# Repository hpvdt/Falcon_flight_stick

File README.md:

# Falcon Flight Stick
A custom-designed **flight control stick** for the Falcon Aircraft project — designing both **hardware and firmware** for force sensing, CAN communication, and USB HID joystick interfacing.

---

## Overview
The **Falcon Flight Stick** is a force-sensing joystick that measures user input via strain gauges and communicates with the aircraft’s control system through **CAN bus** or to a computer host via **USB-C**.  
This project demonstrates my ability to proficiently design, route, and program an embedded system from the ground up — including power delivery, signal integrity, and firmware architecture.

---

## Key Features
- **MCU Core:** STM32F103CBU6 managing all board-level events with an external 8Mhz Oscillator
- **Sensing System:** Three strain gauges read via a precision Texas Instruments ADS131M03IRUK ADC (32-bit SPI interface)  
- **Connectivity:**  
  - USB-C (HID joystick or virtual COM port)  
  - CAN bus daisy-chain communication  
- **Memory:** 1×128-byte EEPROM for calibration data 
- **Power System:**  
  - TI TPS62177 step-down converter for higher current ditial power
  - ADI LT1962 LDO (3.3V)  for low noise, low current analog power
  - Automatic protection between USB-C and LiPo (12V) sources 
- **PCB Stackup:** 4-layer board with separated analog/digital planes for signal integrity
- **Breakout Button Matrix:**
  - button matrix allowing for a hotswappable and fully customizable button interface on the joystick
  - Up to 25 individual buttons, all allowable for interrupts

---

## Hardware Design

### Hardware Repository
The latest hardware version is **Falcon Flight Stick Rev5**.  
Previous revisions were experimental or undocumented.

### Design Breakdown

The STM32 MCU is programmed through **ST-LinkV3 (SWD)** and communicates via **UART** for debug and development.  
Differential USB data lines enable HID or COM functionality, depending on firmware.  

Strain gauge signals are processed through a TI ADC, which triggers SPI reads via a DRDY interrupt.  
Processed values are sent to the servo controller board (via CAN) or USB interface.  

---

## Power Architecture

The power subsystem ensures stable operation from multiple sources:
- **12V LiPo (CAN chain)** or **5V USB-C**
- Both inputs are protected from backfeed
- Outputs:  
  - 3.3V Digital (MCU, logic)  
  - 3.3V Analog (ADC, strain gauge front-end)

These rails are physically isolated to minimize noise and ground-reference drift.

---

## Schematics
Full schematic set:  

---

## PCB Layout

### Summary
- 4-layer stackup for power and noise isolation  
- Separated analog/digital ground and power planes  
- Power trace widths sized by current draw  
- Labelled parts for developer readability  

### Views
**Full Layout:**  

**Layer 1: Signal**  

**Layer 2: Power**  

**Layer 3: GND / AGND**  

**Layer 4: Signal 2**  

---

## 3D Model

---

## Firmware (Planned / In Progress)

Example outline:
- USB HID joystick emulation via STM32 HAL  
- CAN message handling for actuator control  
- ADC data acquisition and digital filtering  
- EEPROM calibration storage  

---

## Tools Used
- **KiCad 8.0** – PCB and schematic design  
- **STM32CubeIDE** – Firmware development  & MCU pinout planning
- **JLCPCB** – Fabrication and assembly  
- **SolidWorks** – 3D mechanical integration  
- **GitHub / Git** – Version control  

---

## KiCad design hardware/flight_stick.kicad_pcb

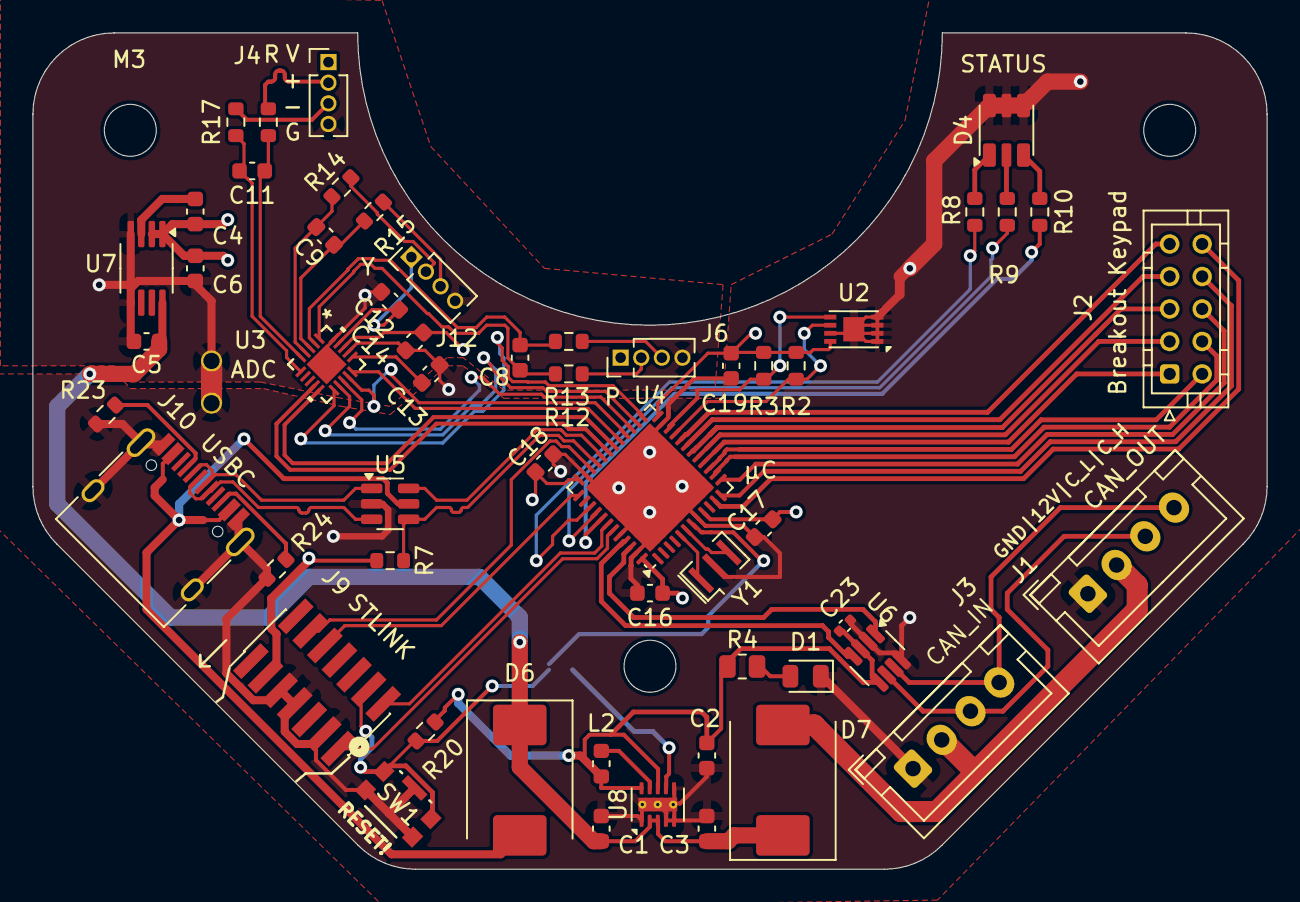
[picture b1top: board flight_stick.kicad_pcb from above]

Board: 4 copper layers, 76.0 x 51.5 mm, 60 parts (1 on the bottom side), 66 nets.

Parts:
C1, C3: 2.2u; C_0603_1608Metric
C2: 22u; C_0603_1608Metric
C4: 10n; C_0603_1608Metric
C5: 1u; C_0603_1608Metric
C6: 4.7u; C_0603_1608Metric
C8, C9, C11, C12, C14, C16, C17, C18, C19: 100n; C_0603_1608Metric
C13: 220n; C_0603_1608Metric
C23: 1u; C_0402_1005Metric
D1: GREEN_LED; LED_0805_2012Metric
D4: SMLVN6RGB; LED_ROHM_SMLVN6
D6, D7: SS34; D_SMC
H1, H2, H3: MountingHole; MountingHole_3.2mm_M3
J1, J3: Conn_01x04_Male; JST_XH_B4B-XH-A_1x04_P2.50mm_Vertical
J2: Conn_02x05_Odd_Even; JST_PHD_B10B-PHDSS_2x05_P2.00mm_Vertical
J4: Load Cell 3; PinHeader_1x04_P1.27mm_Vertical
J6: Load Cell 1; PinHeader_1x04_P1.27mm_Vertical
J9: Conn_ST_STDC14; PinHeader_2x07_P1.27mm_Vertical_SMD
J10: USB_C_Receptacle_USB2.0; USB_C_Receptacle_HRO_TYPE-C-31-M-12
J12: Load Cell 2; PinHeader_1x04_P1.27mm_Vertical
JP1: SolderJumper; SolderJumper-2_P1.3mm_Open_TrianglePad1.0x1.5mm
L2: 10uH; L_0603_1608Metric
NT1: NetTie_2; NetTie-2_THT_Pad1.0mm
R2, R3: 4.7k; R_0603_1608Metric
R4: 400; R_0805_2012Metric
R7: 1.5k; R_0603_1608Metric
R8, R9, R10: 200; R_0603_1608Metric
R12, R13, R14, R15, R16, R17: 1k; R_0603_1608Metric
R20: 10k; R_0603_1608Metric
R23, R24: 5.1K; R_0603_1608Metric
SW1: KMR223G LFG; KMR2_G_CNK
U2: AT24CS01-MAHM; DFN-8-1EP_3x2mm_P0.5mm_EP1.3x1.5mm
U3: ADS131M03IRUKx; QFN_WQFN_RUK_TEX
U4: STM32F103CBU6; QFN-48-1EP_7x7mm_P0.5mm_EP5.6x5.6mm
U5: USBLC6-2SC6; SOT-23-6
U6: TCAN3403; TSOT-23-8
U7: LT1962-3.3; MSOP-8_3x3mm_P0.65mm
U8: TPS62177DQC; WSON-10-1EP_2x3mm_P0.5mm_EP0.84x2.4mm_ThermalVias
Y1: 8M; Resonator_SMD_Murata_CSTxExxV-3Pin_3.0x1.1mm

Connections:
+3.3V: C2.1, C14.1, C16.2, C17.2, C18.2, C19.1, C23.1, J9.3 (VCC), L2.2, R2.1, R3.1, R4.1, R7.1, R20.1, U2.8 (VCC), U3.18 (DVDD), U4.9 (VDDA), U4.24 (VDD), U4.36 (VDD), U4.48 (VDD), U6.3 (V_{CC}), U6.5 (V_{IO}), U8.8 (~SLEEP), U8.10 (VOS)
+3.3VA: C4.1, C6.1, C12.1, J4.1, J6.1, J12.1, U3.19 (AVDD), U7.1 (OUT), U7.2 (SENSE)
+5V: D6.2 (A), J10.A4 (VBUS), J10.A9 (VBUS), J10.B4 (VBUS), J10.B9 (VBUS), U5.5 (VBUS)
+12V: D7.2 (A), J1.2, J3.2
/ADC_CS: U3.10 (~CS), U4.30 (PA9)
/ADC_DRDY: U3.11 (DRDY), U4.25 (PB12)
/ADC_MCO: U3.15 (CLKIN), U4.29 (PA8)
/ADC_MISO: U3.13 (DOUT), U4.27 (PB14)
/ADC_MOSI: U3.14 (DIN), U4.28 (PB15)
/ADC_RST: U3.9 (~RESET), U4.31 (PA10)
/ADC_SCK: U3.12 (SCLK), U4.26 (PB13)
/CAN_IO/CAN_H: J1.4, J3.4, U6.7 (CANH)
/CAN_IO/CAN_L: J1.3, J3.3, U6.6 (CANL)
/CAN_RX: U4.45 (PB8), U6.4 (RXD)
/CAN_TX: U4.46 (PB9), U6.1 (TXD)
/COMPRT_RX: J9.13 (VCP_RX), U4.43 (PB7)
/COMPRT_TX: J9.14 (VCP_TX), U4.42 (PB6)
/D+: J10.A6 (D+), J10.B6 (D+), U5.3 (I/O2)
/D-: J10.A7 (D-), J10.B7 (D-), U5.1 (I/O1)
/EEPROM_SCK: R2.2, U2.6 (SCL), U4.21 (PB10)
/EEPROM_SDA: R3.2, U2.5 (SDA), U4.22 (PB11)
/MTX_COL1: J2.2, U4.15 (PA5)
/MTX_COL2: J2.4, U4.14 (PA4)
/MTX_COL3: J2.6, U4.13 (PA3)
/MTX_COL4: J2.8, U4.12 (PA2)
/MTX_COL5: J2.10, U4.11 (PA1)
/MTX_ROW1: J2.1, U4.16 (PA6)
/MTX_ROW2: J2.3, U4.17 (PA7)
/MTX_ROW3: J2.5, U4.18 (PB0)
/MTX_ROW4: J2.7, U4.19 (PB1)
/MTX_ROW5: J2.9, U4.20 (PB2)
/OSC+: U4.5 (PD0), Y1.1
/OSC-: U4.6 (PD1), Y1.3
/PRC_DIO: J9.4 (JTMS/SWDIO), U4.34 (PA13)
/PRG_CLK: J9.6 (JCLK/SWCLK), U4.37 (PA14)
/Power/Vin_{pwr}: C1.1, C3.1, C5.1, D6.1 (K), D7.1 (K), U7.8 (IN), U8.2 (VIN), U8.3 (EN)
/RGB_B: R8.1, U4.39 (PB3)
/RGB_G: R10.1, U4.41 (PB5)
/RGB_R: R9.1, U4.40 (PB4)
/USBN: U4.32 (PA11), U5.6 (I/O1)
/USBP: R7.2, U4.33 (PA12), U5.4 (I/O2)
/~RESET: J9.12 (~RST), JP1.1 (A), R20.2, SW1.1, SW1.2, U4.7 (NRST)
GND: C1.2, C2.2, C3.2, C13.2, C14.2, C16.1, C17.1, C18.1, C19.2, C23.2, D1.1 (K), D4.4 (GK), D4.5 (RK), D4.6 (BK), J1.1, J3.1, J9.5 (GND), J9.7 (GND), J9.11 (GNDDetect), J10.A1 (GND), J10.A12 (GND), J10.B1 (GND), J10.B12 (GND), J10.S1 (SHIELD), NT1.2, R23.1, R24.1, SW1.3, SW1.4, SW1.5, U2.1 (A0), U2.2 (A1), U2.3 (A2), U2.4 (GND), U2.7 (WP), U2.9 (GND), U3.17 (DGND), U4.8 (VSSA), U4.23 (VSS), U4.35 (VSS), U4.44 (BOOT0), U4.47 (VSS), U4.49 (VSS), U5.2 (GND), U6.2 (GND), U6.8 (STB), U8.1 (PGND), U8.4 (NC), U8.5 (FB), U8.6 (AGND), U8.11 (PAD), Y1.2
GNDA: C5.2, C6.2, C12.2, J4.4, J6.4, J12.4, NT1.1, U3.20 (AGND), U3.21 (AGND), U7.4 (GND), U7.5 (~SHDN)
unnamed: D1.2 (A), R4.2
unnamed: D4.1 (BA), R8.2
unnamed: D4.3 (GA), R10.2
unnamed: D4.2 (RA), R9.2
unnamed: J4.2, R16.1
unnamed: J4.3, R17.1
unnamed: J6.2, R12.1
unnamed: J6.3, R13.1
unnamed: J10.A5 (CC1), R23.2
unnamed: J10.B5 (CC2), R24.2
unnamed: J12.2, R14.1
unnamed: J12.3, R15.1
unnamed: JP1.2 (B), U8.7 (PG)
unnamed: C8.1, R13.2, U3.2 (AIN0N)
unnamed: C8.2, R12.2, U3.1 (AIN0P)
unnamed: C9.1, R15.2, U3.3 (AIN1N)
unnamed: C9.2, R14.2, U3.4 (AIN1P)
unnamed: C11.1, R17.2, U3.6 (AIN2N)
unnamed: C11.2, R16.2, U3.5 (AIN2P)
unnamed: C13.1, U3.16 (CAP)
unnamed: C4.2, U7.3 (BYP)
unnamed: L2.1, U8.9 (SW)

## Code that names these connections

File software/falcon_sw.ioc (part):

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Mcu.Name=STM32F103CBUx
Mcu.Package=UFQFPN48
Mcu.UserName=STM32F103CBUx
PA1.GPIOParameters=GPIO_Label
PA1.GPIO_Label=MTX_COL5
PA1.Signal=GPIO_Output
PA10.GPIOParameters=GPIO_Label
PA10.GPIO_Label=ADC_RST
PA10.Signal=GPIO_Output
PA11.Mode=Device
PA11.Signal=USB_DM
PA12.Mode=Device
PA12.Signal=USB_DP
PA13.Mode=Serial_Wire
PA13.Signal=SYS_JTMS-SWDIO
PA14.Mode=Serial_Wire
PA14.Signal=SYS_JTCK-SWCLK
PA2.GPIOParameters=GPIO_Label
PA2.GPIO_Label=MTX_COL4
PA2.Signal=GPIO_Output
PA3.GPIOParameters=GPIO_Label
PA3.GPIO_Label=MTX_COL3
PA3.Signal=GPIO_Output
PA4.GPIOParameters=GPIO_Label
PA4.GPIO_Label=MTX_COL2
PA4.Signal=GPIO_Output
PA5.GPIOParameters=GPIO_Label
PA5.GPIO_Label=MTX_COL1
PA5.Signal=GPIO_Output
PA6.GPIOParameters=GPIO_Label
PA6.GPIO_Label=MTX_ROW1
PA6.Signal=GPIO_Input
PA7.GPIOParameters=GPIO_Label
PA7.GPIO_Label=MTX_ROW2
PA7.Signal=GPIO_Input
PA8.Mode=Clock-out
PA8.Signal=RCC_MCO
PA9.GPIOParameters=GPIO_Label
PA9.GPIO_Label=ADC_CS
PA9.Signal=GPIO_Output
PB0.GPIOParameters=GPIO_Label
PB0.GPIO_Label=MTX_ROW3
PB0.Signal=GPIO_Input
PB1.GPIOParameters=GPIO_Label
PB1.GPIO_Label=MTX_ROW4
PB1.Signal=GPIO_Input
PB10.GPIOParameters=GPIO_Label
PB10.GPIO_Label=EEP_I2C2_SCL
PB10.Mode=I2C
PB10.Signal=I2C2_SCL
PB11.GPIOParameters=GPIO_Label
PB11.GPIO_Label=EEP_I2C2_SDA
PB11.Mode=I2C
PB11.Signal=I2C2_SDA
PB12.GPIOParameters=GPIO_Label
PB12.GPIO_Label=ADC_DRDY_EXTI12
PB12.Signal=GPXTI12
PB13.Mode=Full_Duplex_Master
PB13.Signal=SPI2_SCK
PB14.Mode=Full_Duplex_Master
PB14.Signal=SPI2_MISO
PB15.Mode=Full_Duplex_Master
PB15.Signal=SPI2_MOSI
PB2.GPIOParameters=GPIO_Label
PB2.GPIO_Label=MTX_ROW5
PB2.Signal=GPIO_Input
PB3.Signal=S_TIM2_CH2
PB4.Signal=S_TIM3_CH1
PB5.GPIOParameters=GPIO_Label
PB5.GPIO_Label=RGB_PIN
PB5.Signal=GPIO_Output
PB6.Mode=Asynchronous
PB6.Signal=USART1_TX
PB7.Mode=Asynchronous
PB7.Signal=USART1_RX
PB8.Mode=CAN_Activate
PB8.Signal=CAN_RX
PB9.Mode=CAN_Activate
PB9.Signal=CAN_TX
PD0-OSC_IN.Mode=HSE-External-Oscillator
PD0-OSC_IN.Signal=RCC_OSC_IN
PD1-OSC_OUT.Mode=HSE-External-Oscillator
PD1-OSC_OUT.Signal=RCC_OSC_OUT
RCC.SYSCLKFreq_VALUE=48000000
RCC.SYSCLKSource=RCC_SYSCLKSOURCE_PLLCLK
board=custom

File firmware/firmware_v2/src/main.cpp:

/**
 * Falcon Flight Stick firmware_v2
 * STM32F103CBU6: UART hello + peripheral status, then loop: poll ADC -> 16-bit -> serial + RGB.
 *
 * Pinout:
 *   UART:    PB6 (TX), PB7 (RX)  - USART1 remapped
 *   ADC SPI: PB13 (SCLK), PB14 (MISO), PB15 (MOSI), CS=PA9, RESET=PA10, DRDY=PB12, MCO=PA7
 *   EEPROM:  PB10 (SCL), PB11 (SDA) - I2C2
 *   RGB:     PB3 (Blue), PB4 (Red), PB5 (Green)
 */

#include <Arduino.h>
#include <SPI.h>
#include <Wire.h>

// ---- UART (COM port via ST-Link) ----
#define UART_RX  PB7
#define UART_TX  PB6
HardwareSerial SerialUart(UART_RX, UART_TX);

// ---- ADC (ADS131M03) ----
#define ADC_CS    PA9
#define ADC_RST   PA10
#define ADC_DRDY  PB12
#define ADC_MCO   PA7
#define ADC_SCK   PB13
#define ADC_MISO  PB14
#define ADC_MOSI  PB15

SPIClass adc_spi(ADC_MOSI, ADC_MISO, ADC_SCK);

// ---- RGB LED ----
#define RGB_BLUE  PB3
#define RGB_RED   PB4
#define RGB_GREEN PB5

// ---- EEPROM I2C ----
#define EEPROM_SCL PB10
#define EEPROM_SDA PB11
#define EEPROM_ADDR 0x50

// ---- Timing ----
#define LOOP_DELAY_MS  2500

static void initUart(void);
static void initRgb(void);
static void initAdc(void);
static bool probeEeprom(void);
static void printStatus(bool adc_ok, bool eeprom_ok);
static void readAdcChannels(uint16_t* ch0, uint16_t* ch1, uint16_t* ch2);
static void setRgbFromAdc(uint16_t ch0, uint16_t ch1, uint16_t ch2);

void setup() {
  initUart();
  SerialUart.println("Hello");

  SerialUart.println("initRgb...");
  initRgb();
  SerialUart.println("initAdc...");
  initAdc();

  // Probe ADC: try one read (can block if ADC not connected / wrong wiring)
  SerialUart.println("readAdc...");
  uint16_t c0, c1, c2;
  readAdcChannels(&c0, &c1, &c2);
  bool adc_ok = (c0 != 0xFFFF && c1 != 0xFFFF && c2 != 0xFFFF) ||
                (c0 != 0x0000 && c1 != 0x0000 && c2 != 0x0000);  // avoid all 0 or all 1 as "no response"
  SerialUart.println("eeprom...");
  bool eeprom_ok = probeEeprom();

  printStatus(adc_ok, eeprom_ok);
}

void loop() {
  uint16_t ch0, ch1, ch2;
  readAdcChannels(&ch0, &ch1, &ch2);

  SerialUart.print("CH0=");
  SerialUart.print(ch0);
  SerialUart.print(" CH1=");
  SerialUart.print(ch1);
  SerialUart.print(" CH2=");
  SerialUart.println(ch2);

  setRgbFromAdc(ch0, ch1, ch2);
  delay(LOOP_DELAY_MS);
}

static void initUart(void) {
  SerialUart.begin(115200);
  while (!SerialUart)
    ;
}

static void initRgb(void) {
  pinMode(RGB_BLUE, OUTPUT);
  pinMode(RGB_RED, OUTPUT);
  pinMode(RGB_GREEN, OUTPUT);
  digitalWrite(RGB_BLUE, LOW);
  digitalWrite(RGB_RED, LOW);
  digitalWrite(RGB_GREEN, LOW);
}

static void initAdc(void) {
  pinMode(ADC_MCO, OUTPUT);
  RCC->CFGR &= ~RCC_CFGR_MCO;
  RCC->CFGR |= RCC_CFGR_MCO_SYSCLK;

  pinMode(ADC_CS, OUTPUT);
  pinMode(ADC_RST, OUTPUT);
  pinMode(ADC_DRDY, INPUT);
  digitalWrite(ADC_CS, HIGH);
  digitalWrite(ADC_RST, HIGH);

  digitalWrite(ADC_RST, LOW);
  delay(10);
  digitalWrite(ADC_RST, HIGH);
  delay(10);

  adc_spi.begin();
  delay(50);  // let ADC settle after reset before first SPI read
}

static bool probeEeprom(void) {
  Wire.begin((int)EEPROM_SDA, (int)EEPROM_SCL);
#if defined(WIRE_HAS_TIMEOUT)
  Wire.setWireTimeout(500, true);  // 500 us, reset on timeout so we don't hang
#endif
  Wire.beginTransmission((uint8_t)EEPROM_ADDR);
  uint8_t err = Wire.endTransmission();
  return (err == 0);
}

static void printStatus(bool adc_ok, bool eeprom_ok) {
  SerialUart.print("ADC: ");
  SerialUart.println(adc_ok ? "OK" : "FAIL");
  SerialUart.print("EEPROM: ");
  SerialUart.println(eeprom_ok ? "OK" : "FAIL/skip");
  SerialUart.println("RGB: OK");
  SerialUart.println("---");
}

/**
 * ADS131M03: 3 channels, 24-bit each. SPI frame: send null cmd (0x2000), read status + 3×24-bit.
 * We use 16-bit transfers: 1 status + 6 words for CH0/CH1/CH2 (each channel = 2×16-bit, 24-bit data).
 * 24-bit value = (high_word << 8) | (low_word >> 8). Normalize to 16-bit: take top 16 bits (>> 8).
 */
static void readAdcChannels(uint16_t* ch0, uint16_t* ch1, uint16_t* ch2) {
  digitalWrite(ADC_CS, LOW);
  delayMicroseconds(1);

  const uint16_t null_cmd = 0x2000;
  uint16_t w0 = adc_spi.transfer16(null_cmd);  // status
  uint16_t w1 = adc_spi.transfer16(null_cmd);  // CH0 high
  uint16_t w2 = adc_spi.transfer16(null_cmd);  // CH0 low
  uint16_t w3 = adc_spi.transfer16(null_cmd);  // CH1 high
  uint16_t w4 = adc_spi.transfer16(null_cmd);  // CH1 low
  uint16_t w5 = adc_spi.transfer16(null_cmd);  // CH2 high
  uint16_t w6 = adc_spi.transfer16(null_cmd);  // CH2 low

  digitalWrite(ADC_CS, HIGH);

  (void)w0;
  uint32_t v0_24 = ((uint32_t)w1 << 8) | (w2 >> 8);
  uint32_t v1_24 = ((uint32_t)w3 << 8) | (w4 >> 8);
  uint32_t v2_24 = ((uint32_t)w5 << 8) | (w6 >> 8);

  *ch0 = (uint16_t)(v0_24 >> 8);
  *ch1 = (uint16_t)(v1_24 >> 8);
  *ch2 = (uint16_t)(v2_24 >> 8);
}

/** CH0->R, CH1->G, CH2->B. Simple: above threshold (e.g. mid-scale) turn on, else off. */
static void setRgbFromAdc(uint16_t ch0, uint16_t ch1, uint16_t ch2) {
  const uint16_t thresh = 32768;
  digitalWrite(RGB_RED,   ch0 > thresh ? HIGH : LOW);
  digitalWrite(RGB_GREEN, ch1 > thresh ? HIGH : LOW);
  digitalWrite(RGB_BLUE,  ch2 > thresh ? HIGH : LOW);
}

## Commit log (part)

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2025-08-16 Added REV5 flightstick
2025-08-16 added new voltage reg
2025-08-17 Upload of old firmware
2025-08-18 Added subpages and CAN tranciever
2025-08-18 Fixed ERC errors & CAN module
2025-08-21 Added EEPROM, resolved comments
2025-08-21 Stylistic changes
2025-08-22 revamped button matrix
2025-08-22 Finished footprint assignment and deleted pcb
2025-08-22 Began layout placement
2025-10-03 modified mcu pin alloc and pre-routing placement
2025-10-03 Completed first layout draft
2025-10-03 small changes
2025-10-05 resolved comments
2025-10-06 Updated footprints
2025-10-08 updated comments
2025-10-08 tied PG to mcu reset
2025-10-08 clean up traces
2025-10-08 Refactor netlist and lock footprints in PCB design
    Renamed the /RESET net to /~{RESET} and updated all references accordingly. Reordered and renumbered net definitions to maintain consistency. Added the 'locked' attribute to multiple footprints for i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
2025-10-08 changed to in-stock buck regulator
2025-10-08 Update PCB and Gerber files for new U8 footprint
    Removed an obsolete drawing from the PCB and regenerated all Gerber and production files to reflect the addition of a new U8 footprint. Also deleted an outdated Gerber ZIP archive.
2025-10-08 Remove hardware\jlcpcb from .gitignore
2025-10-09 README overhaul
2025-10-09 Add PCB sheet schematic
2025-10-14 changed 0402 cap part # and regenerated prod files
2025-10-18 Add image to README
2025-10-18 Resize images in README.md
    Updated images in README to improve display size.
2025-10-18 Improve README.md formatting
    Added a blank line for better readability.
2025-10-18 Update README with new images and formatting
    Added additional images to the README and updated formatting.
2025-10-23 Initialize software dev
2025-10-23 Changed PWM pin to GPIO for successful LED blink sanity test
2026-02-13 Add visible ground layer for Layer 1 and Layer 4 in README
    Added additional images for Layer 1 and Layer 4 in the README.
